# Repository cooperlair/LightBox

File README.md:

# LightBox
Prototyping Project utilizing CAD/ECAD skills

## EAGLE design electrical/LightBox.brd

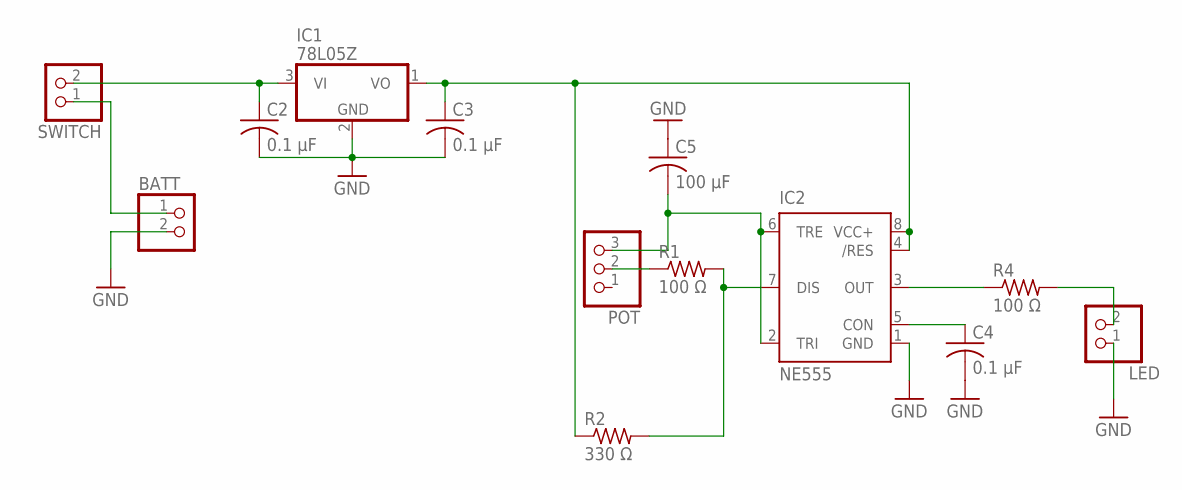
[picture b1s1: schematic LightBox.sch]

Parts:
BATT: PINHD-1X2; 1X02
C2, C3, C4: 0.1 µF; C0805
C5: 100 µF; C025-024X044
IC1: 78L05Z; TO92
IC2: NE555; DIL-08
LED: PINHD-1X2; 1X02
POT: PINHD-1X3; 1X03
R1, R4: 100 Ω; R0805
R2: 330 Ω; R0805
SWITCH: PINHD-1X2; 1X02

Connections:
GND: BATT.2, C2.2, C3.2, C4.2, C5.1, IC1.2 (GND), IC2.1 (GND), LED.1
unnamed: C5.2, IC2.2 (TRI), IC2.6 (TRE), POT.3
unnamed: IC2.7 (DIS), R1.2, R2.2
unnamed: IC2.3 (OUT), R4.1
unnamed: LED.2, R4.2
unnamed: C2.1, IC1.3 (VI), SWITCH.2
unnamed: C4.1, IC2.5 (CON)
unnamed: BATT.1, SWITCH.1
unnamed: C3.1, IC1.1 (VO), IC2.4 (/RES), IC2.8 (VCC+), R2.1
unnamed: POT.2, R1.1

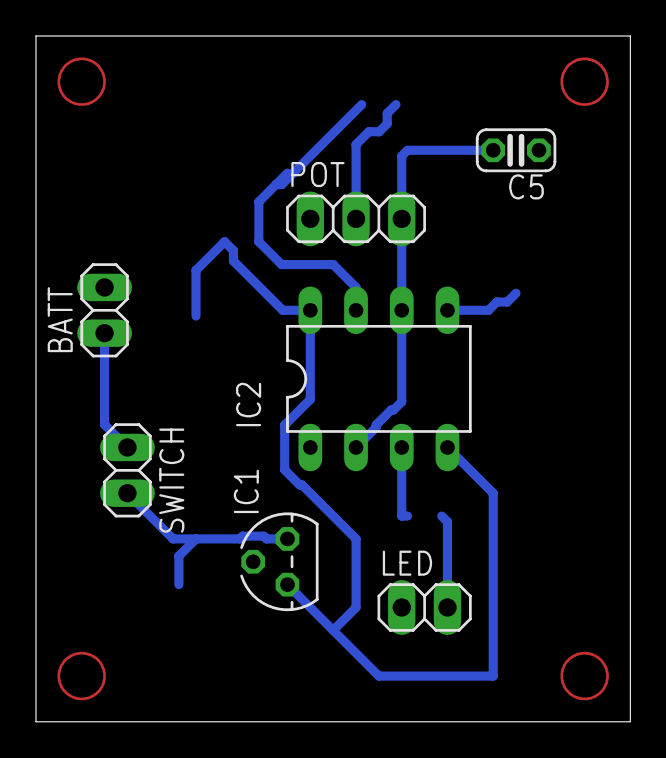
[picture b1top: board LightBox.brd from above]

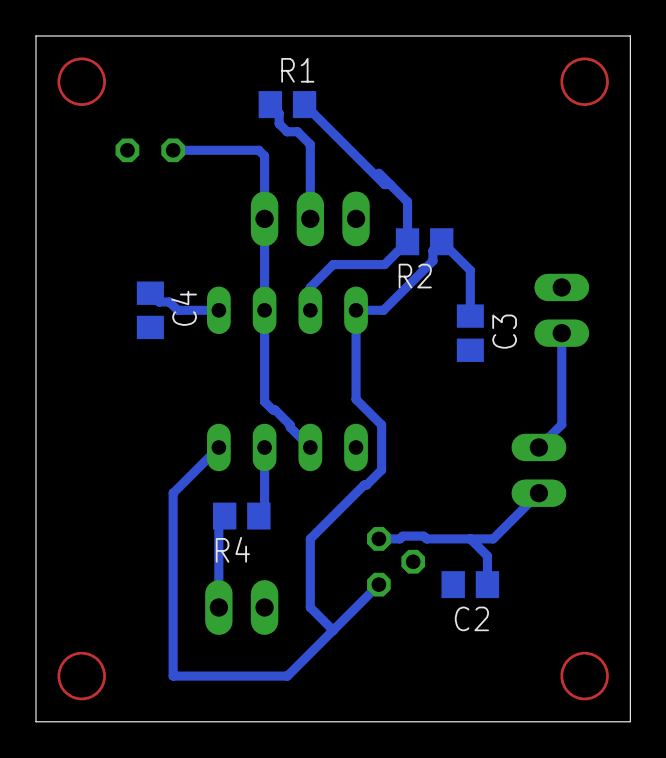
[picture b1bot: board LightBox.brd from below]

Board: 2 copper layers, 33.0 x 38.1 mm, 13 parts (6 on the bottom side), 10 nets.

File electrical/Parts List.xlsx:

Part | # | Value | Size | Cost
Resistor | 2 | 100 Ω | 0805 (SMD)
Resistor | 1 | 330 Ω | 0805 (SMD)
Capacitor | 3 | 0.1 µF | 0805 (SMD)
Capacitor | 1 | 100 µF | 24 x 44 mm
7805 Voltage Regulator | 1 | N/A
Battery | 1 | 9 V
Switch | 1
LED | 1
Potentiometer | 1 | 10 kΩ
555 Timer | 1
